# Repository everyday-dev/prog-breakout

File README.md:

# We've moved. 
In an effort to truly own and be in full control of our clients and personal information, source code, and documentation we've moved to a self-hosted Git server. You can find this project here: [git.everydaydev.io](https://git.everydaydev.io/opensource/prog-breakout)

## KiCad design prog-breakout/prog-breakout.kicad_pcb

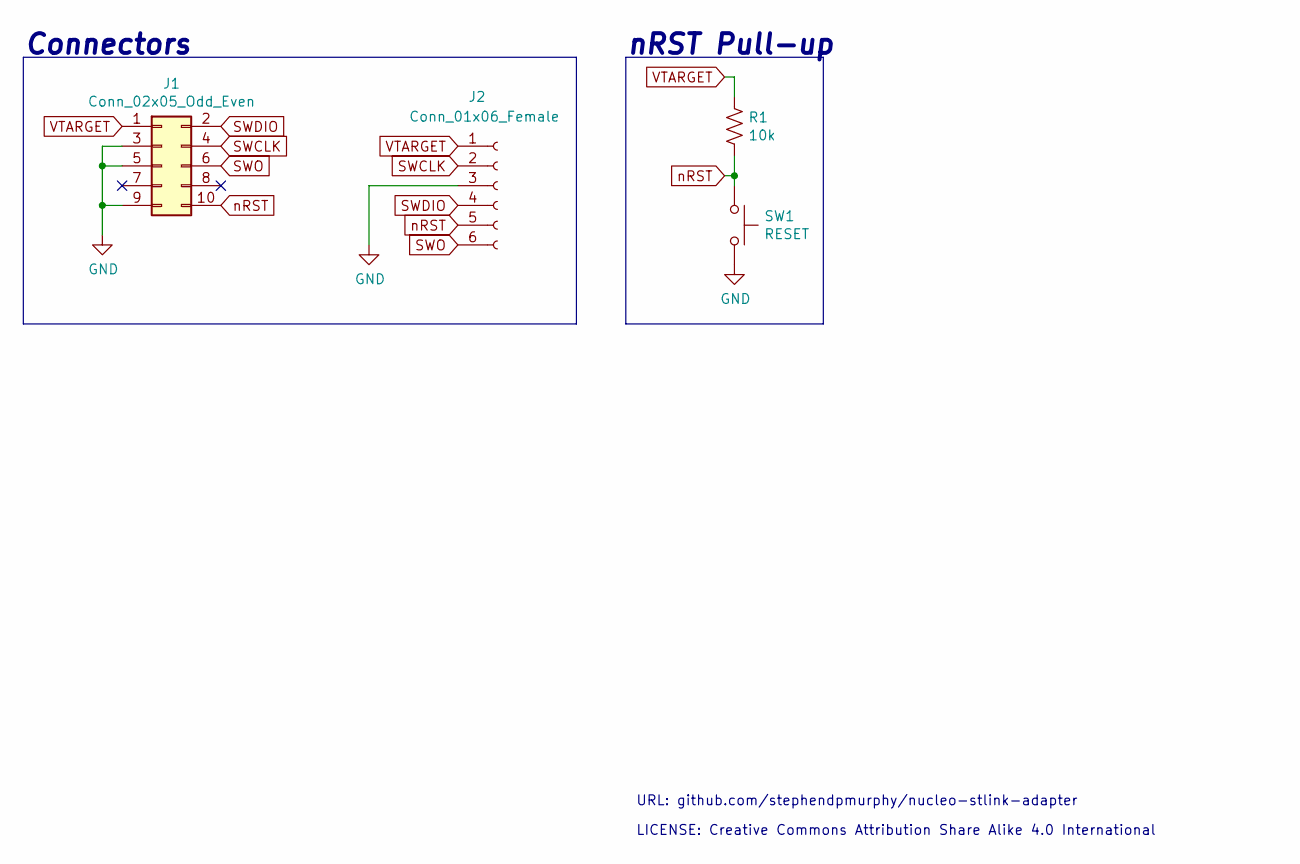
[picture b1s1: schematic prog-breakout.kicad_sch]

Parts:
J1: Conn_02x05_Odd_Even; PinHeader_2x05_P1.27mm_Vertical_SMD
J2: Conn_01x06_Female; PinHeader_1x06_P2.54mm_Vertical
R1: 10k; R_0603_1608Metric
SW1: RESET; SW_SPST_TL3342

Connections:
GND: J1.3, J1.5, J1.9, J2.3, SW1.2
SWCLK: J1.4, J2.2
SWDIO: J1.2, J2.4
SWO: J1.6, J2.6
VTARGET: J1.1, J2.1, R1.2
nRST: J1.10, J2.5, R1.1, SW1.1

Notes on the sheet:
nRST Pull-up
Connectors
LICENSE: Creative Commons Attribution Share Alike 4.0 International
URL: github.com/stephendpmurphy/nucleo-stlink-adapter

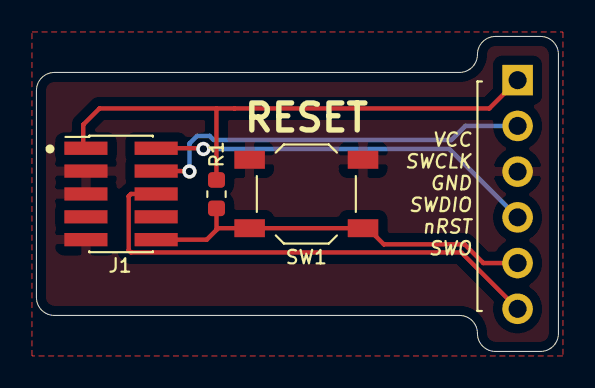
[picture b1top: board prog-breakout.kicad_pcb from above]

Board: 2 copper layers, 29.0 x 17.5 mm, 4 parts (1 on the bottom side), 6 nets.

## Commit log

2020-07-28 Committing rev 1
2020-07-28 Updating README.md
2020-08-21 Cleaned up schematic and board
2020-10-05 Updating license
2022-12-30 Updating naming and .gitignore
2022-12-30 Cleaned up README
2022-12-30 Added gld logo to bottom side

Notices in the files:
prog-breakout/prog-breakout.kicad_pcb:
CC-BY-SA
